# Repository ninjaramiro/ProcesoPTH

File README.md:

# ProcesoPTH
 PTH = Plated Trough Hole = Agujero (pasante) metalizado

Este repositorio documenta un sistema para metalizar con cobre agujeros de un circuito impreso.

El proceso consiste en la preparación de los agujeros para que puedan ser metalizados mediante una deposición electroquímica de un metal disuelto en una solución acuosa.

Los pasos del proceso son:

* Perforación de la placa virgen con cobre en ambas caras

* Tratamiento químico de los agujeros para eliminar imperfecciones del mecanizado

* Deposición de la solución activadora y pirólisis

* Electrodeposición

Actualizado 2019-05-10 18:32

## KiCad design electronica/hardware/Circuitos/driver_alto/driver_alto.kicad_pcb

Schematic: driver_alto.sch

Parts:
C1, C2: 470uFx35V; CP_Radial_D12.5mm_P5.00mm
C3, C4, C5, C6, C7, C8, C9: 0.1uF; C_0603_1608Metric_Pad1.05x0.95mm_HandSolder
C10, C11: 100uFx35V; CP_Radial_D10.0mm_P5.00mm
D1, D2: 1N4007; D_DO-35_SOD27_P7.62mm_Horizontal
D3: LED_VE; LED_0603_1608Metric_Pad1.05x0.95mm_HandSolder
D4: LED_RO; LED_0603_1608Metric_Pad1.05x0.95mm_HandSolder
D5: LED_AM; LED_0603_1608Metric_Pad1.05x0.95mm_HandSolder
J1: ALIM_AC; TerminalBlock_MetzConnect_Type086_RT03403HBLC_1x03_P3.81mm_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
J2: DISPARO; TIRA_PINES_1X3
J3: SWITCH; TerminalBlock_MetzConnect_Type086_RT03402HBLC_1x02_P3.81mm_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
J4: ALIM_CC; TIRA_PINES_1X3
M1, M2, M3, M4: AGUJERO_MONTAJE; MountingHole_3.2mm_M3
Q1: 2N7002; SOT-23
R1, R2, R6, R7: 1K; R_0603_1608Metric_Pad1.05x0.95mm_HandSolder
R3: 2K2; R_0603_1608Metric_Pad1.05x0.95mm_HandSolder
R4: 390; R_0603_1608Metric_Pad1.05x0.95mm_HandSolder
R5: 4.7; R_0603_1608Metric_Pad1.05x0.95mm_HandSolder
U1: LM7815_TO220; TO-220-3_Vertical
U2: LM7915_TO220; TO-220-3_Vertical
U3: UCC23513; SO-6_7.5mm_X_4.7mm

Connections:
/VCC: C6.1, C8.1, C10.1, D4.2, J4.3, U1.3 (VO), U3.6
/VDD: C3.2, D3.2, J2.1, R4.2
/VEE: C7.1, C9.2, C11.1, D5.1, J4.1, U2.3 (VO), U3.4
GND: C3.1, J2.2, Q1.2 (S), R1.1, R3.1
GNDREF: C1.2, C2.2, C4.2, C5.2, C6.2, C7.2, C8.2, C9.1, C10.2, C11.2, J1.2, J3.2, J4.2, R6.1, R7.1, U1.2 (GND), U2.1 (GND)
unnamed: C1.1, C4.1, D1.1, U1.1 (VI)
unnamed: C2.1, C5.1, D2.2, U2.2 (VI)
unnamed: D1.2, J1.1
unnamed: D2.1, J1.3
unnamed: D3.1, R1.2
unnamed: D4.1, R6.2
unnamed: D5.2, R7.2
unnamed: J2.3, R2.2
unnamed: J3.1, R5.1
unnamed: Q1.1 (G), R2.1, R3.2
unnamed: Q1.3 (D), U3.3
unnamed: R4.1, U3.1
unnamed: R5.2, U3.5

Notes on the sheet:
PLACA IMPRESA DOBLE FAZ 39MM X 45 MM

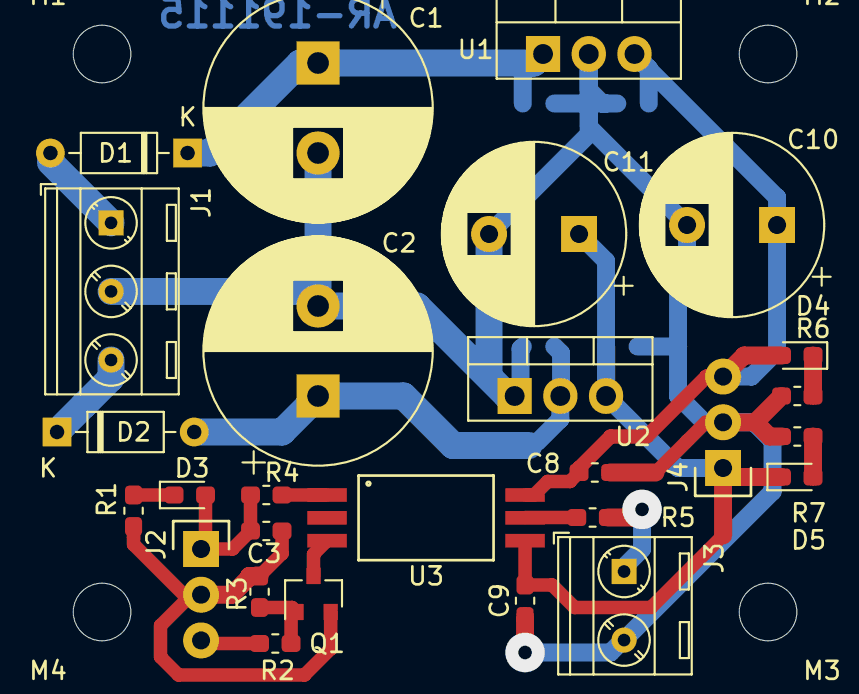
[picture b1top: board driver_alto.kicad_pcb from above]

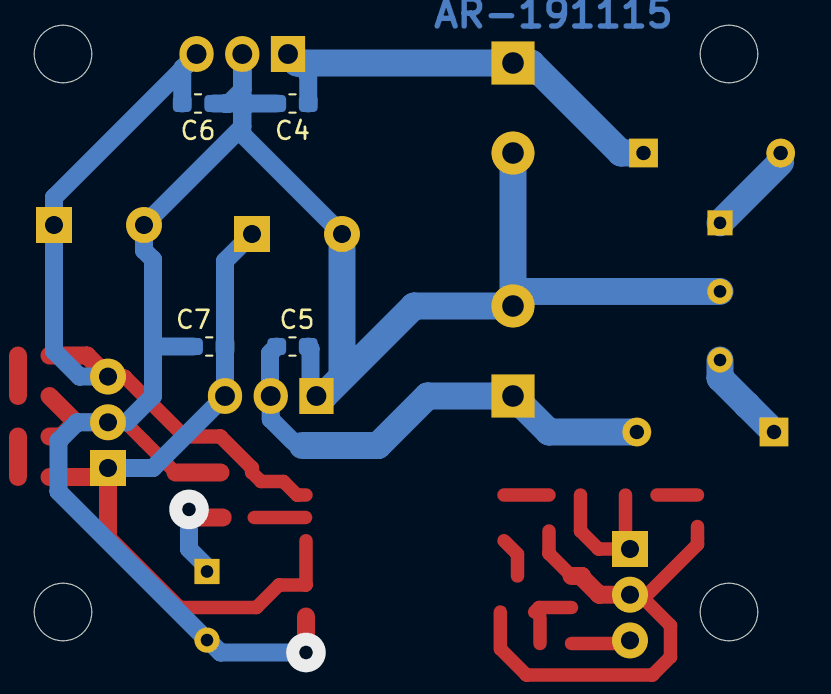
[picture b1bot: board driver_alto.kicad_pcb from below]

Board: 2 copper layers, 35 parts (4 on the bottom side), 18 nets.

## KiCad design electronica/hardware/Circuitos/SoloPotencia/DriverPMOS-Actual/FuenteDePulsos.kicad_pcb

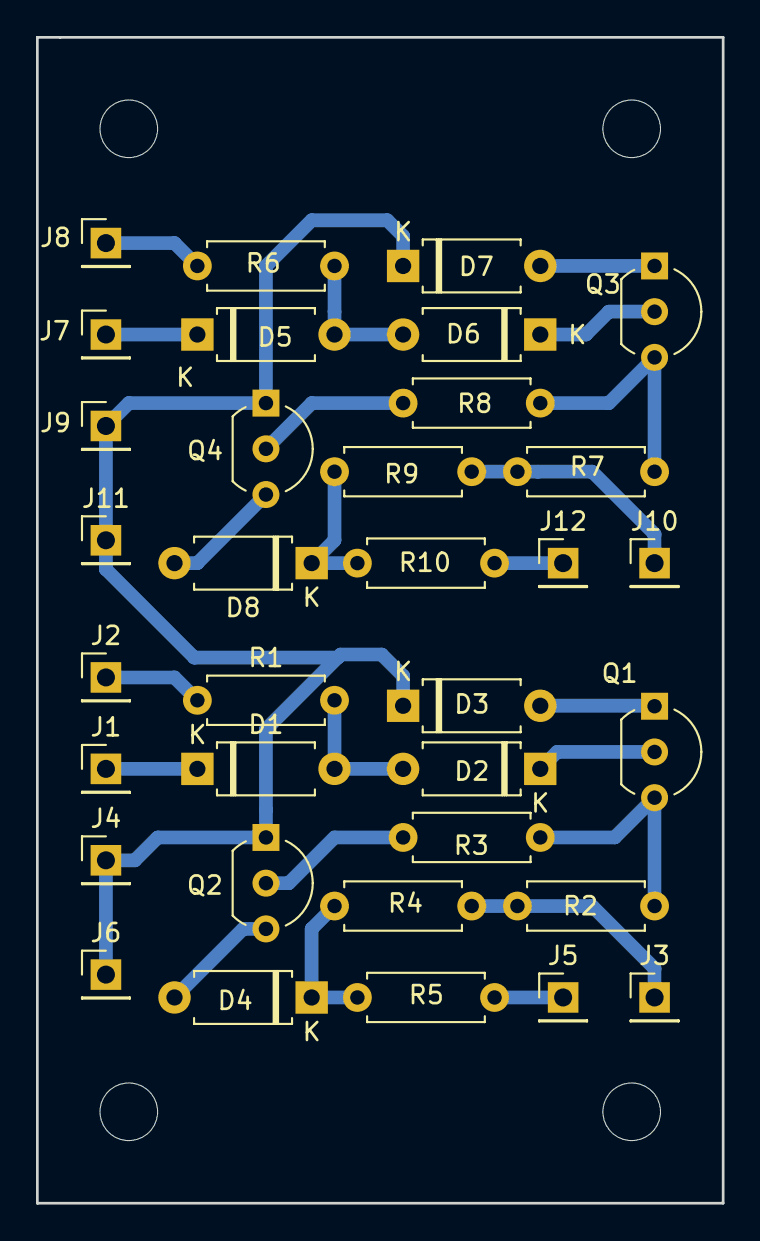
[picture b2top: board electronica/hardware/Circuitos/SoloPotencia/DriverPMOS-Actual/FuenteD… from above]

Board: 2 copper layers, 38.1 x 64.8 mm, 38 parts (0 on the bottom side), 23 nets.

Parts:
D1, D2, D3, D5, D6, D7: 1N4148; D_A-405_P7.62mm_Horizontal
D4, D8: 12v; D_A-405_P7.62mm_Horizontal
H1, H2, H3, H4: MountingHole; MountingHole_3.2mm_M3
J1, J2, J3, J4, J5, J6, J7, J8, J9, J10, J11, J12: Conn_01x01; PinHeader_1x01_P2.54mm_Vertical
Q1, Q3: BC548; TO-92_Inline_Wide
Q2, Q4: 2n2907 o BC327; TO-92_Inline_Wide
R1, R2, R6, R7: 4k7; R_Axial_DIN0207_L6.3mm_D2.5mm_P7.62mm_Horizontal
R3, R8: 100; R_Axial_DIN0207_L6.3mm_D2.5mm_P7.62mm_Horizontal
R4, R9: 180; R_Axial_DIN0207_L6.3mm_D2.5mm_P7.62mm_Horizontal
R5, R10: 22; R_Axial_DIN0207_L6.3mm_D2.5mm_P7.62mm_Horizontal

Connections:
GND: D3.1, D7.1, J4.1, J6.1, J9.1, J11.1, Q2.1, Q4.1
unnamed: D1.1, J1.1
unnamed: D1.2, D2.2, R1.2
unnamed: D2.1, Q1.2
unnamed: D3.2, Q1.1
unnamed: D4.1, R4.1, R5.1
unnamed: D4.2, Q2.3
unnamed: D5.1, J7.1
unnamed: D5.2, D6.2, R6.2
unnamed: D6.1, Q3.2
unnamed: D7.2, Q3.1
unnamed: D8.1, R9.1, R10.1
unnamed: D8.2, Q4.3
unnamed: J2.1, R1.1
unnamed: J3.1, R2.2, R4.2
unnamed: J5.1, R5.2
unnamed: J8.1, R6.1
unnamed: J10.1, R7.2, R9.2
unnamed: J12.1, R10.2
unnamed: Q1.3, R2.1, R3.2
unnamed: Q2.2, R3.1
unnamed: Q3.3, R7.1, R8.2
unnamed: Q4.2, R8.1

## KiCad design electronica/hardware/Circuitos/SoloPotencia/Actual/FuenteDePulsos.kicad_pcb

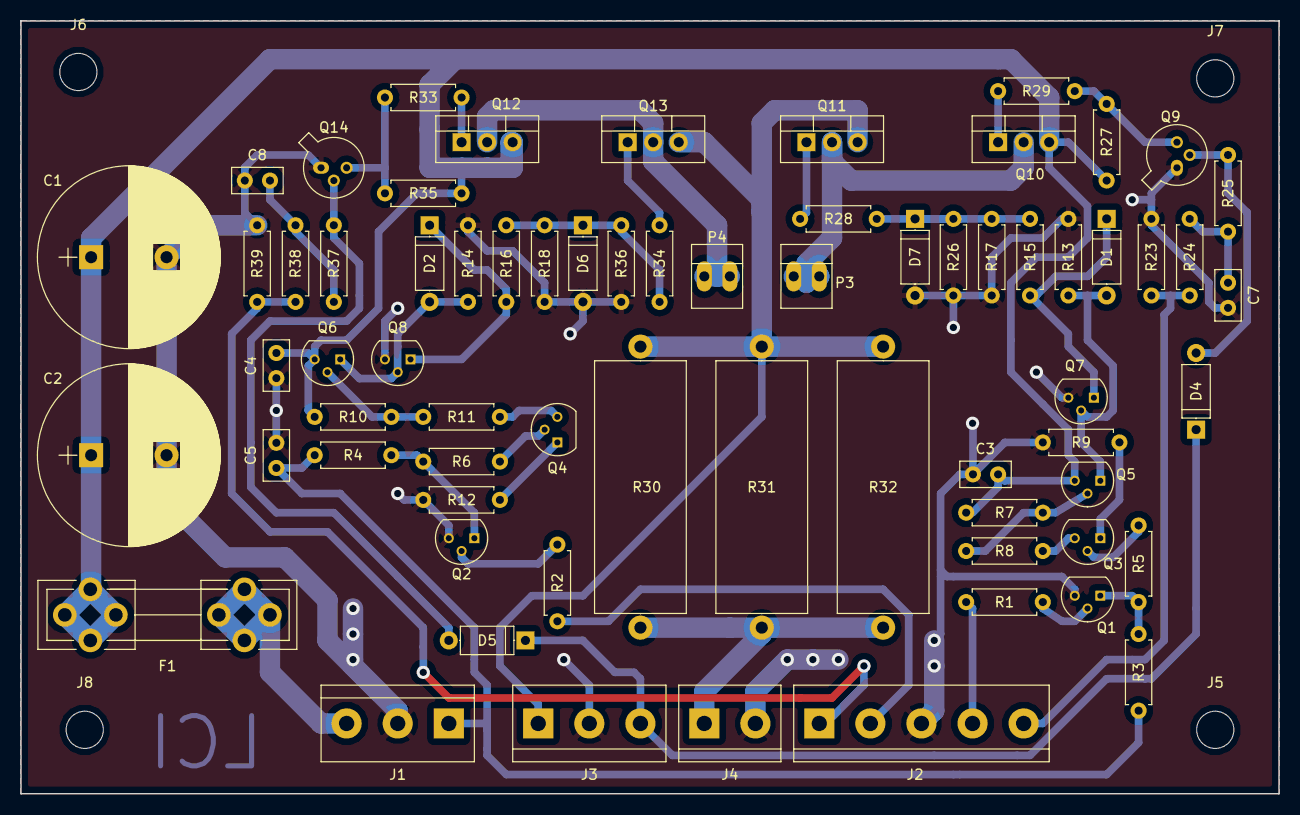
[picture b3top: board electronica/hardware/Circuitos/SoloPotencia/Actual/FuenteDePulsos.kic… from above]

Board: 2 copper layers, 125.1 x 76.8 mm, 73 parts (0 on the bottom side), 41 nets.

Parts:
C1, C2: 2200uFx35V; CP_Radial_D18.0mm_P7.50mm
C3, C4, C5: 100nF; C_Disc_D5.0mm_W2.5mm_P2.50mm
C7, C8: C; C_Disc_D5.0mm_W2.5mm_P2.50mm
D1, D2, D4, D5: 1N4148; D_A-405_P7.62mm_Horizontal
D6, D7: Dz 18v; D_A-405_P7.62mm_Horizontal
F1: FUSE; Fuseholder5x20_horiz_open_universal_Type-III
J1, J3: Conn_01x03; TerminalBlock_bornier-3_P5.08mm
J2: Conn_01x05; TerminalBlock_bornier-5_P5.08mm
J4: ACS712; TerminalBlock_bornier-2_P5.08mm
J5, J6, J7, J8: Agujero; MountingHole_3.7mm
P3: SALIDA_1; PINHEAD1-2
P4: SALIDA_2; PINHEAD1-2
Q1, Q2, Q7, Q8: 2N3906; TO-92_Molded_Narrow
Q3, Q4: 2N3904; TO-92_Molded_Narrow
Q5, Q6: BC327; TO-92_Molded_Narrow
Q9, Q14: 2N2222; TO-18-3
Q10, Q12: TIP127; TO-220-3_Vertical
Q11, Q13: IRFZ46N; TO-220-3_Vertical
R1, R2, R5, R6, R8, R11: 1k; R_Axial_DIN0207_L6.3mm_D2.5mm_P7.62mm_Horizontal
R3, R4, R7, R10, R13, R14: 4k7; R_Axial_DIN0207_L6.3mm_D2.5mm_P7.62mm_Horizontal
R9, R12, R17, R18: 1k8; R_Axial_DIN0207_L6.3mm_D2.5mm_P7.62mm_Horizontal
R15, R16: 22; R_Axial_DIN0207_L6.3mm_D2.5mm_P7.62mm_Horizontal
R23, R26, R27, R35, R36, R39: 10k; R_Axial_DIN0207_L6.3mm_D2.5mm_P7.62mm_Horizontal
R24, R38: 330; R_Axial_DIN0207_L6.3mm_D2.5mm_P7.62mm_Horizontal
R25, R37: 100; R_Axial_DIN0207_L6.3mm_D2.5mm_P7.62mm_Horizontal
R28, R29, R33, R34: 470; R_Axial_DIN0207_L6.3mm_D2.5mm_P7.62mm_Horizontal
R30, R31, R32: 0.1; R_Axial_Power_L25.0mm_W9.0mm_P27.94mm

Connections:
+5V: C5.1, J1.1, R3.1, R4.1
+24V: C1.1, C2.1, C3.1, C4.1, F1.2, Q5.3, Q6.3, Q10.3, Q12.3, R7.1, R10.1, R27.2, R35.2
/Circuito_pulsos/Corr_sens: J3.1, Q11.3, Q13.3, R30.1, R31.1, R32.1
/Circuito_pulsos/Limitador_corriente: D4.1, D5.1, J3.3
/Circuito_pulsos/PWM1: D7.1, R15.1, R17.2, R26.1, R28.2
/Circuito_pulsos/PWM2: D6.1, R16.1, R18.2, R34.2, R36.1
/PWM1: J2.4, R1.2
/PWM2: J2.2, R2.2
/Pulso1: J2.5, R23.2, R24.2
/Pulso2: J2.1, R38.2, R39.2
GND: C1.2, C2.2, C3.2, C4.2, C5.2, C7.2, C8.2, D6.2, D7.2, J1.2, J2.3, J3.2, J4.2, Q1.3, Q2.3, Q7.3, Q8.3, Q9.1, Q14.1, R9.1, R12.1, R13.2, R14.2, R17.1, R18.1, R23.1, R26.2, R36.2, R39.1
unnamed: C7.1, R24.1, R25.2
unnamed: C8.1, R37.2, R38.1
unnamed: D1.1, Q7.1, R15.2
unnamed: D1.2, Q5.1, Q7.2, R13.1
unnamed: D2.1, Q8.1, R16.2
unnamed: D2.2, Q6.1, Q8.2, R14.1
unnamed: D4.2, Q9.2, R25.1
unnamed: D5.2, Q14.2, R37.1
unnamed: F1.1, J1.3
unnamed: J4.1, R30.2, R31.2, R32.2
unnamed: P3.1, P3.2, Q10.2, Q11.2
unnamed: P4.1, P4.2, Q12.2, Q13.2
unnamed: Q1.1, R3.2, R5.2
unnamed: Q1.2, R1.1
unnamed: Q2.1, R4.2, R6.2
unnamed: Q2.2, R2.1
unnamed: Q3.1, R9.2
unnamed: Q3.2, R5.1
unnamed: Q3.3, R8.1
unnamed: Q4.1, R12.2
unnamed: Q4.2, R6.1
unnamed: Q4.3, R11.1
unnamed: Q5.2, R7.2, R8.2
unnamed: Q6.2, R10.2, R11.2
unnamed: Q9.3, R27.1, R29.1
unnamed: Q10.1, R29.2
unnamed: Q11.1, R28.1
unnamed: Q12.1, R33.2
unnamed: Q13.1, R34.1
unnamed: Q14.3, R33.1, R35.1

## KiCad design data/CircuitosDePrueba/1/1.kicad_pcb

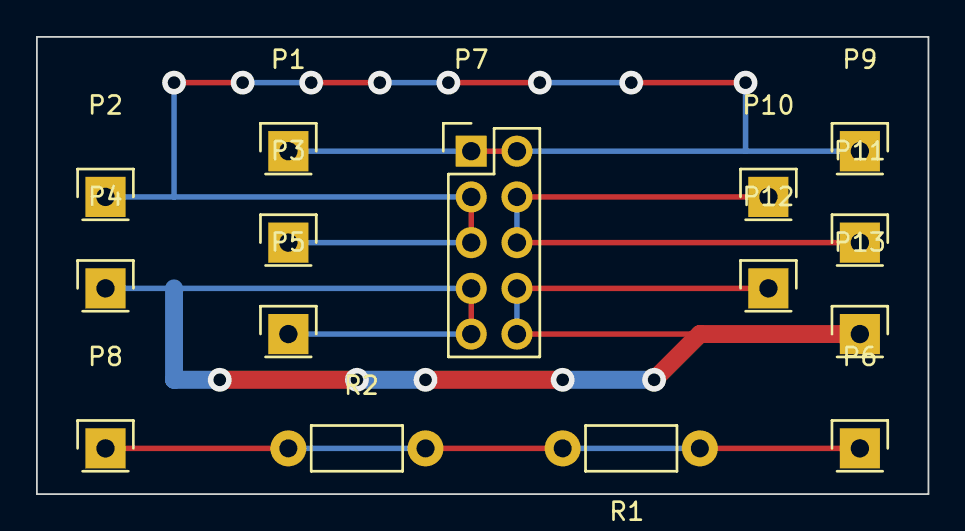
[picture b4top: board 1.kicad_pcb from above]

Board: 2 copper layers, 49.5 x 25.4 mm, 15 parts (0 on the bottom side), 5 nets.

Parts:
P1, P2, P3, P4, P5, P6, P8, P9, P10, P11, P12, P13: CONN_01X01; Pin_Header_Straight_1x01
P7: CONN_02X05; Pin_Header_Straight_2x05
R1, R2: R; Resistor_Horizontal_RM7mm

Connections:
unnamed: P1.1, P2.1, P3.1, P7.1, P7.2, P7.3, P7.5, P9.1
unnamed: P4.1, P5.1, P7.7, P7.9
unnamed: P6.1, P8.1, R1.1, R1.2, R2.1, R2.2
unnamed: P7.4, P7.6, P10.1, P11.1
unnamed: P7.8, P7.10, P12.1, P13.1

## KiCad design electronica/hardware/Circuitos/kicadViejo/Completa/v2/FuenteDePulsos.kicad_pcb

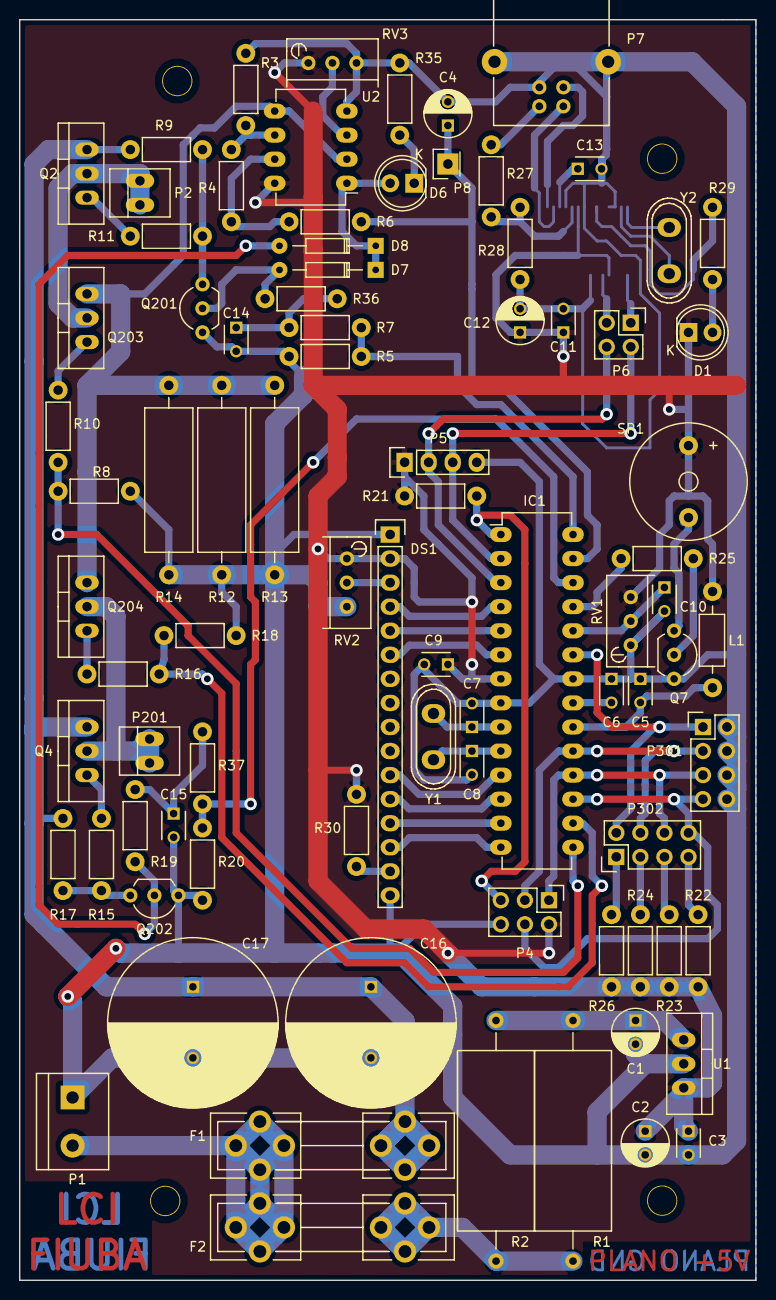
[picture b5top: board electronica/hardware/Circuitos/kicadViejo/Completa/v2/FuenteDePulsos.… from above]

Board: 2 copper layers, 77.7 x 133.1 mm, 89 parts (1 on the bottom side), 68 nets.

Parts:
C1, C2: 100uF 50v; C_Radial_D5_L11_P2.5
C3, C5, C6, C9, C10, C11, C13: 100n; C_Disc_D3_P2.5
C4, C12: 10uF; C_Radial_D5_L11_P2.5
C7, C8: 22p; C_Disc_D3_P2.5
C14, C15: C; C_Disc_D3_P2.5
C16, C17: 2200uFx35V; C_Radial_D18_L36_P7.5
D1, D6: LED; LED-5MM
D7, D8: 1N4148; Diode_DO-35_SOD27_Horizontal_RM10
DS1: LCD16X2; Pin_Header_Straight_1x16
F1, F2: FUSE; Fuseholder5x20_horiz_open_universal_Type-III
IC1: ATMEGA8-P; DIP-28_W7.62mm_LongPads
L1: INDUCTOR; Choke_Horizontal_RM10mm
P1: Entrada_alimentacion; bornier2
P2: SALIDA_1; PINHEAD1-2
P4: Conector_Prog; Pin_Header_Straight_2x03
P5: Conector_Serial; Pin_Header_Straight_1x04
P6: CONN_02X02; Pin_Header_Straight_2x02
P7: USB_B
P8: CONN_01X01; Pin_Header_Straight_1x01
P16, P17, P18, P19: CONN_01X01; MountingHole_3.2mm_M3
P201: SALIDA_2; PINHEAD1-2
P301: Botones; Pin_Header_Straight_2x04
P302: Puente_botones; Pin_Header_Straight_2x04
Q2, Q4: TIP127; TO-220_Neutral123_Vertical
Q7: BC548; TO-92_Inline_Wide
Q201, Q202: 2N2222; TO-92_Inline_Wide
Q203, Q204: IRFZ46N; TO-220_Neutral123_Vertical
R1, R2: 10; Resistor_Ceramic_Horizontal_L19mm-W8mm-H8mm-p25mm
R3, R6, R25: 1k; Resistor_Horizontal_RM7mm
R4, R5, R8, R9, R17, R18, R20, R21, R22, R23, R24, R26, R28: 10k; Resistor_Horizontal_RM7mm
R7, R30, R37: 330; Resistor_Horizontal_RM7mm
R10, R11, R15, R16, R35: 470; Resistor_Horizontal_RM7mm
R12, R13, R14: 0.1; Resistor_Horizontal_RM20mm
R19, R36: 100; Resistor_Horizontal_RM7mm
R27: 4.7k; Resistor_Horizontal_RM7mm
R29: 270; Resistor_Horizontal_RM7mm
RV1: POT; Potentiometer_Bourns_3296W_3-8Zoll_Inline_ScrewUp
RV2, RV3: 10k; Potentiometer_Bourns_3296W_3-8Zoll_Inline_ScrewUp
SP1: BUZZER; Buzzer_12x9.5RM7.6
U1: LM7805; TO-220_Neutral123_Vertical
U2: LM358; DIP-8_W7.62mm_LongPads
U3: FT232RL; SSOP-28_5.3x10.2mm_Pitch0.65mm
Y1: 8MHz; Crystal_HC50-U_Vertical
Y2: Cristal 12MHz; Crystal_HC50-U_Vertical

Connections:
+5V: C2.1, C3.1, C9.1, C11.1, C12.1, D1.1, DS1.2, IC1.7, L1.2, P4.2, P5.1, R21.1, R22.1, R23.1, R24.1, R26.1, R30.1, RV1.3, RV2.1, RV3.1, SP1.1, U1.3, U2.8, U3.4, U3.20
+24V: C16.1, C17.1, F1.2, Q2.3, Q4.3, R9.2, R17.2
/Circuito_pulsos/Corr_sens: Q203.3, Q204.3, R12.1, R13.1, R14.1, U2.2, U2.5
/Circuito_pulsos/Limitador_corriente_1: D7.2, Q201.2, R36.1
/Circuito_pulsos/Limitador_corriente_2: D8.2, Q202.2, R19.1
/Circuito_pulsos/PWM1: IC1.15, R8.1, R10.2
/Circuito_pulsos/PWM2: IC1.16, R16.2, R18.1
/Circuito_pulsos/SENS_CORRIENTE: C4.1, IC1.27, P8.1, R6.1
/Logica/Bot1: IC1.23, P301.1, P302.2
/Logica/Bot2: IC1.19, P4.3, P301.3, P302.4
/Logica/Bot3: IC1.18, P4.1, P301.5, P302.6
/Logica/Bot4: IC1.17, P4.4, P301.7, P302.8
/Logica/Buzzer: IC1.25, R25.2
/Logica/LCD_D4: DS1.11, IC1.11
/Logica/LCD_D5: DS1.12, IC1.12
/Logica/LCD_D6: DS1.13, IC1.13
/Logica/LCD_D7: DS1.14, IC1.14
/Logica/LCD_E: DS1.6, IC1.6
/Logica/LCD_RS: DS1.4, IC1.4
/Logica/LCD_RW: DS1.5, IC1.5
/Logica/Pulse1: IC1.28, R5.2, R7.2
/Logica/Pulse2: IC1.26, R20.2, R37.2
/Logica/RST: IC1.1, P4.5, R21.2
/Logica/RXD_AVR: IC1.2, P5.3, P6.2
/Logica/RXD_FT232: P6.3, U3.5
/Logica/TXD_AVR: IC1.3, P5.2, P6.4
/Logica/TXD_FT232: P6.1, U3.1
/Logica/sheet58087D8D/D+: P7.3, U3.15
/Logica/sheet58087D8D/D-: P7.2, U3.16
/Logica/sheet58087D8D/LED_UART: R29.2, U3.23
/Logica/sheet58087D8D/Reset: R27.2, R28.1, U3.19
GND: C1.2, C2.2, C3.2, C4.2, C5.1, C6.1, C7.2, C8.2, C9.2, C10.2, C11.2, C12.2, C13.2, C14.2, C15.2, C16.2, C17.2, DS1.1, DS1.16, IC1.8, IC1.22, P1.1, P4.6, P5.4, P7.4, P7.5, P301.2, P301.4, P301.6, P301.8, Q7.3, Q201.1, Q202.1, R3.1, R5.1, R8.2, R12.2, R13.2, R14.2, R18.2, R20.1, R28.2, R35.1, RV1.1, RV2.3, RV3.3, U1.2, U2.4, U3.7, U3.18, U3.21, U3.25, U3.26
unnamed: C1.1, R1.1, R2.1, U1.1
unnamed: C5.2, IC1.20, L1.1
unnamed: C6.2, IC1.21
unnamed: C7.1, IC1.9, Y1.1
unnamed: C8.1, IC1.10, Y1.2
unnamed: C10.1, IC1.24, RV1.2
unnamed: C13.1, U3.17
unnamed: C14.1, R7.1, R36.2
unnamed: C15.1, R19.2, R37.1
unnamed: D1.2, R29.1
unnamed: D6.1, R35.2
unnamed: D6.2, D7.1, D8.1, U2.1
unnamed: DS1.3, RV2.2
unnamed: DS1.15, R30.2
unnamed: F1.1, F2.1, P1.2
unnamed: F2.2, R1.2, R2.2
unnamed: P2.1, P2.2, Q2.2, Q203.2
unnamed: P7.1, R27.1
unnamed: P201.1, P201.2, Q4.2, Q204.2
unnamed: P302.1, R26.2
unnamed: P302.3, R24.2
unnamed: P302.5, R23.2
unnamed: P302.7, R22.2
unnamed: Q2.1, R11.2
unnamed: Q4.1, R15.2
unnamed: Q7.1, SP1.2
unnamed: Q7.2, R25.1
unnamed: Q201.3, R9.1, R11.1
unnamed: Q202.3, R15.1, R17.1
unnamed: Q203.1, R10.1
unnamed: Q204.1, R16.1
unnamed: R3.2, R4.2, U2.6
unnamed: R4.1, R6.2, U2.7
unnamed: RV3.2, U2.3
unnamed: U3.27, Y2.1
unnamed: U3.28, Y2.2

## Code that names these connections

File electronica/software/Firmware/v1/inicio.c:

#include "inicio.h"
#include "macros.h"


/************************************************************************
* Inicio de los puertos
************************************************************************/

void Inicio_Puertos (void) {	/* Funcion de inicio de los puertos de entrada/salida */

/*--------- DIRECCION -----------------------------------------------*/
  DIRECCION_PIN(USART_DDR, USART_RXD, ENTRADA);
	DIRECCION_PIN(USART_DDR, USART_TXD, SALIDA);

  DIRECCION_PIN(BOT_1_DDR, BOT_1, ENTRADA);
  DIRECCION_PIN(BOT_2_DDR, BOT_2, ENTRADA);
  DIRECCION_PIN(BOT_3_DDR, BOT_3, ENTRADA);
  DIRECCION_PIN(BOT_4_DDR, BOT_4, ENTRADA);

  DIRECCION_PIN(POTE_DDR, POTE, ENTRADA);
  DIRECCION_PIN(BUZZER_DDR, BUZZER, SALIDA);
  DIRECCION_PIN(PULSE1_DDR, PULSE1, SALIDA);
  DIRECCION_PIN(PULSE2_DDR, PULSE2, SALIDA);

  DIRECCION_PIN(SENS_CORRIENTE_DDR, SENS_CORRIENTE, ENTRADA);

  DIRECCION_PIN(PWM1_DDR, PWM1, SALIDA);
  DIRECCION_PIN(PWM2_DDR, PWM2, SALIDA);

  DIRECCION_PIN(LCD_RS_DDR, LCD_RS, SALIDA);
  DIRECCION_PIN(LCD_RW_DDR, LCD_RW, SALIDA);
  DIRECCION_PIN(LCD_E_DDR, LCD_E, SALIDA);
  DIRECCION_PIN(LCD_D4_DDR, LCD_D4, SALIDA);
  DIRECCION_PIN(LCD_D5_DDR, LCD_D5, SALIDA);
  DIRECCION_PIN(LCD_D6_DDR, LCD_D6, SALIDA);
  DIRECCION_PIN(LCD_D7_DDR, LCD_D7, SALIDA);

/*--------------------------------------------------------*/
	// PULL_UP_PIN(USART_PORT, USART_RXD, NO);
	// PULL_UP_PIN(USART_PORT, USART_TXD, NO);

  PULL_UP_PIN(BOT_1_PORT, BOT_1, SI);  /* LOS BOTONES LLEVAN PULL UP */
  PULL_UP_PIN(BOT_2_PORT, BOT_2, SI);  /* LOS BOTONES LLEVAN PULL UP */
  PULL_UP_PIN(BOT_3_PORT, BOT_3, SI);  /* LOS BOTONES LLEVAN PULL UP */
  PULL_UP_PIN(BOT_4_PORT, BOT_4, SI);  /* LOS BOTONES LLEVAN PULL UP */

  PULL_UP_PIN(POTE_PORT, POTE, NO);
  PULL_UP_PIN(BUZZER_PORT, BUZZER, NO);

  PULL_UP_PIN(SENS_CORRIENTE_PORT, SENS_CORRIENTE, NO);

  // Estado inicial de los puertos

  CLEAR_BIT(BUZZER_PORT, BUZZER);
  CLEAR_BIT(PULSE1_PORT, PULSE1);
  CLEAR_BIT(PULSE2_PORT, PULSE2);
  CLEAR_BIT(PWM1_PORT, PWM1);
  CLEAR_BIT(PWM2_PORT, PWM2);
  CLEAR_BIT(LCD_RS_PORT, LCD_RS);
  CLEAR_BIT(LCD_RW_PORT, LCD_RW);
  CLEAR_BIT(LCD_E_PORT, LCD_E);
  CLEAR_BIT(LCD_D4_PORT, LCD_D4);
  CLEAR_BIT(LCD_D5_PORT, LCD_D5);
  CLEAR_BIT(LCD_D6_PORT, LCD_D6);
  CLEAR_BIT(LCD_D7_PORT, LCD_D7);

}

/************************************************************************
* Inicio Timer
************************************************************************/
/* Inicio el Timer 0 para interrupcion periodica*/
//
// void Inicio_Timer0 (void) {
// 	TCCR0 = 0b00000011;	// prescaler 64 - 125kHz
// 	SET_BIT (TIMSK,TOIE0);	// habilito la interrupción por overflow
// 	CLEAR_BIT (TIFR, TOV0);		// aseguro que no haya ninguna interrupción por overflow
// }
//
//
// /************************************************************************
// * Inicio PWM
// ************************************************************************/
// void Inicio_PWM (void) {
// TCCR1A = 0b10000001; // Habilito el PWM Modo 1 Salida por OC1A puerto 15
// TCCR1B = 0b00000100;  // Prescaler 256 y clock source
// }

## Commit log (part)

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2019-05-10 actualizo README
2019-05-10 agrego fórmulas químicas de soluciones
2019-05-10 link al sitio del cual salen las fórmulas químicas
2019-05-10 link a blog brasilero con fórmulas químicas
2019-05-10 Se suben todos los archivos que se tienen hasta la fecha. Los archivos relacionados con el sotftware y el circuito se subieron al directorio que les corresponde, y el resto a la carpeta data.
2019-05-10 Se agregó un instructivo sencillo de GIT en /data Se agregó una foto de la placa de la etapa de potencia de la fuente pulsada
2019-05-11 1er tarea: forma de onda de referencia
2019-05-14 Agregué un archivo con Notas del proyecto en documentos
2019-05-24 1er versión de forma de onda x PWM
2019-05-24 JPG de medición con oscilo. del PWM generado
2019-05-24 TODO actualizado
2019-05-24 borro no-archivo to-do
2019-05-24 borro .desktop viejos
2019-05-28 Hay drivers. Tensión de drivers debe ser <20V
2019-06-08 Se agregó un libro de ingeniería de superficies, que tiene una sección de electrolisis y un capitulo de pulsed current.
    Se agregó un paper titulado "Pulse and pulse reverse plating"
2019-06-26 Se agregaron en la carpeta "/quimica/ProcesoPTH/quimica/SolucionElectrolitica/Purificacion del sulfato de cobre comercial" fotos del proceso de purificación del sulfato de cobre, y un txt con anotaci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
2019-09-09 Agregué avances en el proceso de purificacion del sulfato de cobre.
2019-09-11 Se agregaron mediciones a la placa de potencia. Las mediciones con un informe se encuentran en ProcesoPTH/documentacion/MedicionesFuenteDePulsos
2019-10-10 Se agregaron mediciones con el nuevo driver para el transistor PMOS
2019-10-25 Se agregó el último firmware
2019-11-01 Se agregaron anotaciones e imágenes de las mediciones del 01/11/2019 Primer intento de deposición de cobre.
2019-11-08 Se agregaron mediciones del 08/11/2019
    Se actualizó el firmware
2019-11-15 driver alto
    Para manejo aislado de los transistores altos (una placa x cada transistor)
2019-11-19 Se modificó el driver de los PMOS. Se hicieron simulaciones que están en: /ProcesoPTH-GIT/electronica/hardware/Simulaciones/DriverPMOS (circuito de arriba a la derecha)
    Se hicieron pruebas con estas modificaciones y los resultados están en:
    /ProcesoPTH-GIT/electronica/hardware/Mediciones/Mediciones 19-11-2019
2019-11-25 Se agregó una descripcion del proceso de purificación del sulfato de cobre mediante cristalización.
2019-11-29 Se hizo un intento de deposición con corriente pulsada. Se agrego la descripción y los resultados.
2019-12-18 Se agregaron sugerencias de Carlos Herme en un txt dentro del directorio de quimica
2020-03-16 Se agregaron imágenes de las experiencias realizadas.
2022-11-09 Agregué documento con el Link del GIT
2026-02-06 Agregue cosas
2026-05-20 Obtuvimos los quimicos.
2026-05-27 Se agregó documentacion del proceso de obtencion de hipofosfito de calcio.
